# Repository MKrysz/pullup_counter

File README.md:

# Pullup Counter

## About

The main purpose of the project was to automatically count and save the amount of pullups I do to evaluate them later using python script. For this purpose I developed a small device mounted onto the bar. Other features include display for showing how many pullups were already done that day and USB serial port for easy to use interface with the device.

## Hardware

### PCB

Schematic and PCB was made in KiCad.

For the power supply I decided that 2 AAA batteries would be the best choice, as they're easily available and have good volumetric energy density. Embedding the Li-Po battery was out of the table, because the project is stationary and charging wouldn't be possible.

As the brain of the device I went with STM32L0 series microcontroller because of following reasons:

- low power consumption and low operating voltage, which is mandatory in battery operated systems like this
- my familiarity with developing both harware and software development with this series
- affordable price.

I chose a STM32L051C8 as I had few of them lying around.

The MCU has a backup battery used for maintaining operation of RTC clock while main batteries are discharged or being replaced. The amount of pullups are displayed on 7 segment display as it's cheap, small and easy to drive. It's also perfect for displaying numbers which is all It's used here for. For a memory in which I would store my database i used a 512kB SPI Flash - P25Q40H. Communication with the device is done with USB serial port, so I included an USB port and USB-UART converter. I also included a capacitive touch pad and little sensor IC as a way to wake the device up. For detecting pullups I used proximity sesor consisting of IR Led diode and photodiode.

PCBs were manufactured by JLCPCB, and are shown below:

During soldering I found out that I'm out of SMD proximity sensors so I glued a THT one instead. Also, by accident, I soldered PNP transistors instead of NPN. After replacing the transistors I had to connect them to different pins of the MCU as the original ones were blown up.

After assembling and mounting it on the pullup bar:

### Mounting

Mounting is done using 3D-printed mounting system and four pairs of M3 bolts and nuts.

## Software

### Embedded

Project was made in VSCode using [stm32-for-vscode](https://github.com/bmd-studio/stm32-for-vscode) extension. For this project I used [stm32CubeMX](https://www.st.com/en/development-tools/stm32cubemx.html) for generating initialization code. I've also used nimaltd's [drivers for SPI flash memory](https://github.com/nimaltd/w25qxx).

The device must be woken up before every training session, which can be done either by physical button or capacitive touch pad. After that if device haven't detected a pullup within specified time, it goes back to sleep to prolong battery life.

Every pullup series is represented with following struct

```C

typedef struct _entry_struct
{
    uint32_t id; // unique id
    unsigned int count:6; // amount of pullups done in the series

    // timestamp
    unsigned int minute:6;
    unsigned int hour:5;
    unsigned int day:5;
    unsigned int month:4;
    unsigned int year:6;
}entry_t;

```

Because each entry's size is 8 bytes and my flash memory is 512kB the maximum amount of pullups that can be saved within the device is over 65 thousand

### USB User Interface

User interface allows the user for easy change of important parameters, debugging and downloading and  clearing data from device's flash memory. To put device in interface mode, plug it in your computer and restart it. The welcome message should appear. After that you can type 'help' for a list of available commands with short description.

### Data analysis

Python script that reads and interprets data acquired from the device.

Below are shown examples of generated plots:

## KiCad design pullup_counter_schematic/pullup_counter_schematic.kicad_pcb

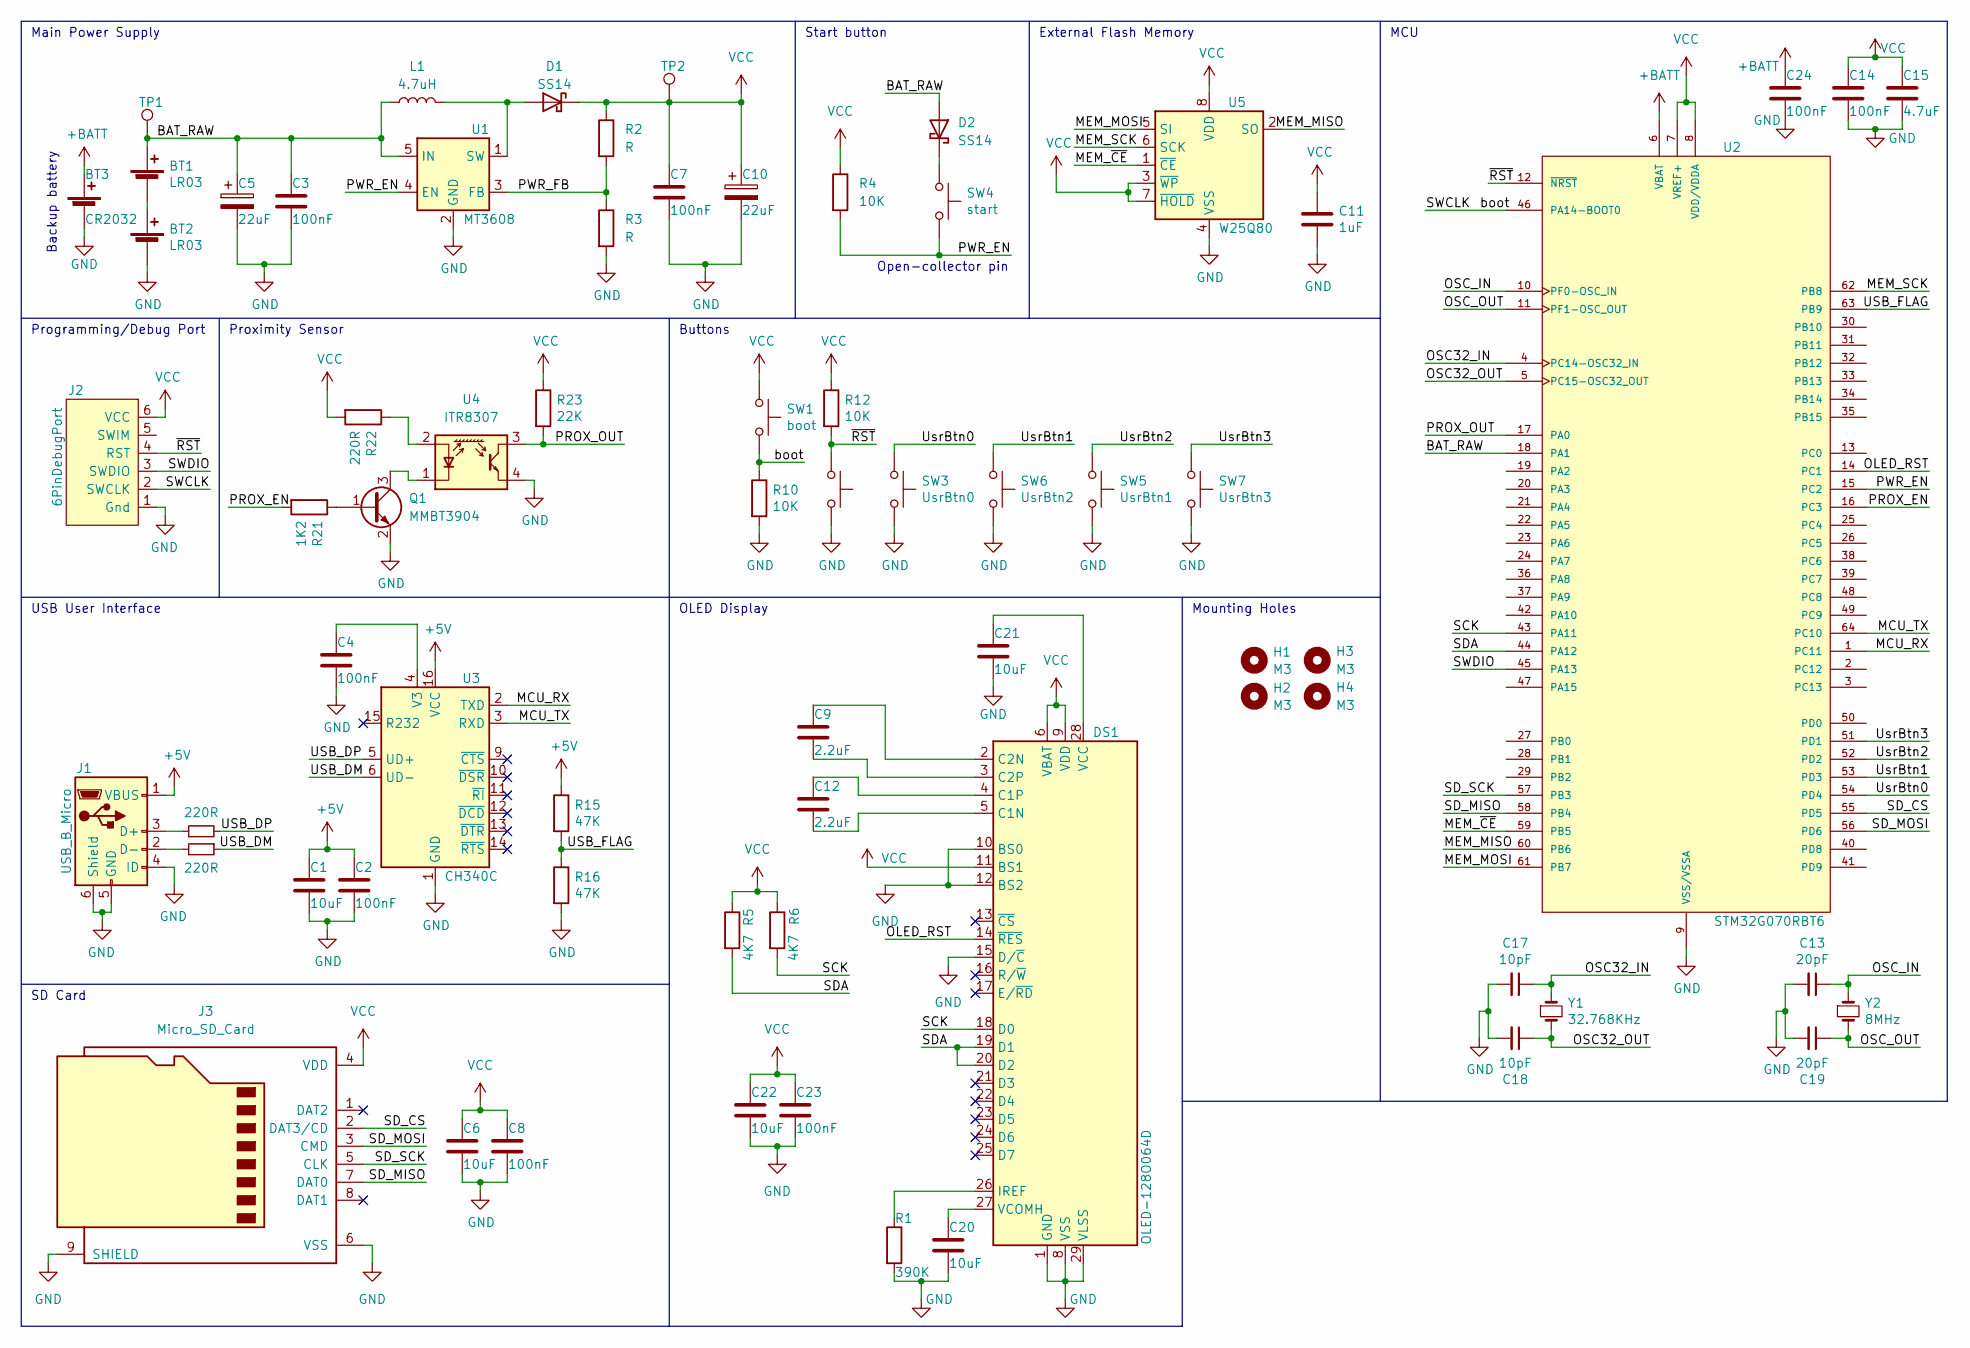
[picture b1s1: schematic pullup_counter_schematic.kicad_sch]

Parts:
BT1, BT2: LR03; SMD_SMT_AAA_LR03
BT3: CR2032; CR2032_CR2025_Battery_Holder
C1, C6, C20, C21, C22: 10uF; C_0805_2012Metric_Pad1.18x1.45mm_HandSolder
C2, C3, C4, C7, C8, C14, C23, C24: 100nF; C_0805_2012Metric_Pad1.18x1.45mm_HandSolder
C5, C10: 22uF; CP_Elec_5x4.5
C9, C12: 2.2uF; C_0805_2012Metric_Pad1.18x1.45mm_HandSolder
C11: 1uF; C_0805_2012Metric_Pad1.18x1.45mm_HandSolder
C13, C19: 20pF; C_0603_1608Metric_Pad1.08x0.95mm_HandSolder
C15: 4.7uF; C_0805_2012Metric_Pad1.18x1.45mm_HandSolder
C17, C18: 10pF; C_0603_1608Metric_Pad1.08x0.95mm_HandSolder
D1, D2: SS14; D_SMA
DS1: OLED-128O064D
H1, H2, H3, H4: M3; MountingHole_3.2mm_M3
J1: USB_B_Micro; USB_Micro-B_Amphenol_10118194_Horizontal
J2: 6PinDebugPort; IDC-Header_2x03_P2.54mm_Vertical
J3: Micro_SD_Card; uSD_socket
L1: 4.7uH; L_Ferrocore_DLG-0403
Q1: MMBT3904; SOT-23
R1: 390K; R_0805_2012Metric_Pad1.20x1.40mm_HandSolder
R2, R3: R; R_0805_2012Metric_Pad1.20x1.40mm_HandSolder
R4, R10, R12: 10K; R_0805_2012Metric_Pad1.20x1.40mm_HandSolder
R5, R6: 4K7; R_0805_2012Metric_Pad1.20x1.40mm_HandSolder
R8, R9, R22: 220R; R_0805_2012Metric_Pad1.20x1.40mm_HandSolder
R15, R16: 47K; R_0805_2012Metric_Pad1.20x1.40mm_HandSolder
R21: 1K2; R_0805_2012Metric_Pad1.20x1.40mm_HandSolder
R23: 22K; R_0805_2012Metric_Pad1.20x1.40mm_HandSolder
SW1: boot; TSB008
SW2: rst; TSB008
SW3: UsrBtn0; TSB008
SW4: start; sw_push_12_x_12_mm
SW5: UsrBtn1; TSB008
SW6: UsrBtn2; TSB008
SW7: UsrBtn3; TSB008
TP1, TP2: PinSocket_1x01_P2.54mm_Vertical
U1: MT3608; SOT-23-6
U2: STM32G070RBT6; LQFP-64_10x10mm_P0.5mm; PARTREV 1
U3: CH340C; SOIC-16_3.9x9.9mm_P1.27mm
U4: ITR8307; Everlight_ITR8307
U5: W25Q80; SOIC-8_5.275x5.275mm_P1.27mm
Y1: 32.768KHz; Crystal_HC49-4H_Vertical
Y2: 8MHz; Crystal_HC49-4H_Vertical

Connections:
+5V: C1.1, C2.1, J1.1 (VBUS), R15.1, U3.16 (VCC)
+BATT: BT3.1 (+), C24.1, U2.6 (VBAT)
/BAT_RAW: BT1.1 (+), C3.1, C5.1, D2.2 (A), L1.1, TP1.1, U1.5 (IN), U2.18 (PA1)
/MCU_RX: U2.1 (PC11), U3.2 (TXD)
/MCU_TX: U2.64 (PC10), U3.3 (RXD)
/MEM_MISO: U2.60 (PB6), U5.2 (SO)
/MEM_MOSI: U2.61 (PB7), U5.5 (SI)
/MEM_SCK: U2.62 (PB8), U5.6 (SCK)
/MEM_~CE: U2.59 (PB5), U5.1 (~CE)
/OLED_RST: DS1.14 (~RES), U2.14 (PC1)
/OSC32_IN: C17.1, U2.4 (PC14-OSC32_IN), Y1.1
/OSC32_OUT: C18.1, U2.5 (PC15-OSC32_OUT), Y1.2
/OSC_IN: C13.1, U2.10 (PF0-OSC_IN), Y2.1
/OSC_OUT: C19.1, U2.11 (PF1-OSC_OUT), Y2.2
/PROX_EN: R21.2, U2.16 (PC3)
/PROX_OUT: R23.2, U2.17 (PA0), U4.3 (C)
/PWR_EN: R4.2, SW4.2, U1.4 (EN), U2.15 (PC2)
/PWR_FB: R2.2, R3.1, U1.3 (FB)
/SCK: DS1.18 (D0), R6.2, U2.43 (PA11)
/SDA: DS1.19 (D1), DS1.20 (D2), R5.2, U2.44 (PA12)
/SD_CS: J3.2 (DAT3/CD), U2.55 (PD5)
/SD_MISO: J3.7 (DAT0), U2.58 (PB4)
/SD_MOSI: J3.3 (CMD), U2.56 (PD6)
/SD_SCK: J3.5 (CLK), U2.57 (PB3)
/SWCLK: J2.2 (SWCLK), R10.1, SW1.2, U2.46 (PA14-BOOT0)
/SWDIO: J2.3 (SWDIO), U2.45 (PA13)
/USB_DM: R9.1, U3.6 (UD-)
/USB_DP: R8.2, U3.5 (UD+)
/USB_FLAG: R15.2, R16.1, U2.63 (PB9)
/UsrBtn0: SW3.1, U2.54 (PD4)
/UsrBtn1: SW6.1, U2.53 (PD3)
/UsrBtn2: SW5.1, U2.52 (PD2)
/UsrBtn3: SW7.1, U2.51 (PD1)
/~RST: J2.4 (RST), R12.2, SW2.1, U2.12 (~NRST)
GND: BT2.2 (-), BT3.2 (-), C1.2, C2.2, C3.2, C4.2, C5.2, C6.2, C7.2, C8.2, C10.2, C11.2, C13.2, C14.2, C15.2, C17.2, C18.2, C19.2, C20.2, C21.2, C22.2, C23.2, C24.2, DS1.1 (GND), DS1.8 (VSS), DS1.10 (BS0), DS1.12 (BS2), DS1.15 (D/~C), DS1.29 (VLSS), DS1.30 (GND), J1.4 (ID), J1.5 (GND), J1.6 (Shield), J2.1 (Gnd), J3.6 (VSS), J3.9 (SHIELD), Q1.2 (E), R1.2, R3.2, R10.2, R16.2, SW2.2, SW3.2, SW5.2, SW6.2, SW7.2, U1.2 (GND), U2.9 (VSS/VSSA), U3.1 (GND), U4.4 (E), U5.4 (VSS)
unnamed: BT1.2 (-), BT2.1 (+)
unnamed: C4.1, U3.4 (V3)
unnamed: C9.1, DS1.2 (C2N)
unnamed: C9.2, DS1.3 (C2P)
unnamed: C12.1, DS1.4 (C1P)
unnamed: C12.2, DS1.5 (C1N)
unnamed: C20.1, DS1.27 (VCOMH)
unnamed: D1.2 (A), L1.2, U1.1 (SW)
unnamed: D2.1 (K), SW4.1
unnamed: DS1.26 (IREF), R1.1
unnamed: C21.1, DS1.28 (VCC)
unnamed: J1.2 (D-), R9.2
unnamed: J1.3 (D+), R8.1
unnamed: Q1.1 (B), R21.1
unnamed: Q1.3 (C), U4.1 (K)
unnamed: R22.1, U4.2 (A)
VCC: C6.1, C7.1, C8.1, C10.1, C11.1, C14.1, C15.1, C22.1, C23.1, D1.1 (K), DS1.6 (VBAT), DS1.9 (VDD), DS1.11 (BS1), J2.6 (VCC), J3.4 (VDD), R2.1, R4.1, R5.1, R6.1, R12.1, R22.2, R23.1, SW1.1, TP2.1, U2.7 (VREF+), U2.8 (VDD/VDDA), U5.3 (~WP), U5.7 (~HOLD), U5.8 (VDD)

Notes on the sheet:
OLED Display
USB User Interface
Main Power Supply
Programming/Debug Port
Open-collector pin
Backup battery
External Flash Memory
MCU
Start button
Proximity Sensor
Mounting Holes
SD Card
Buttons

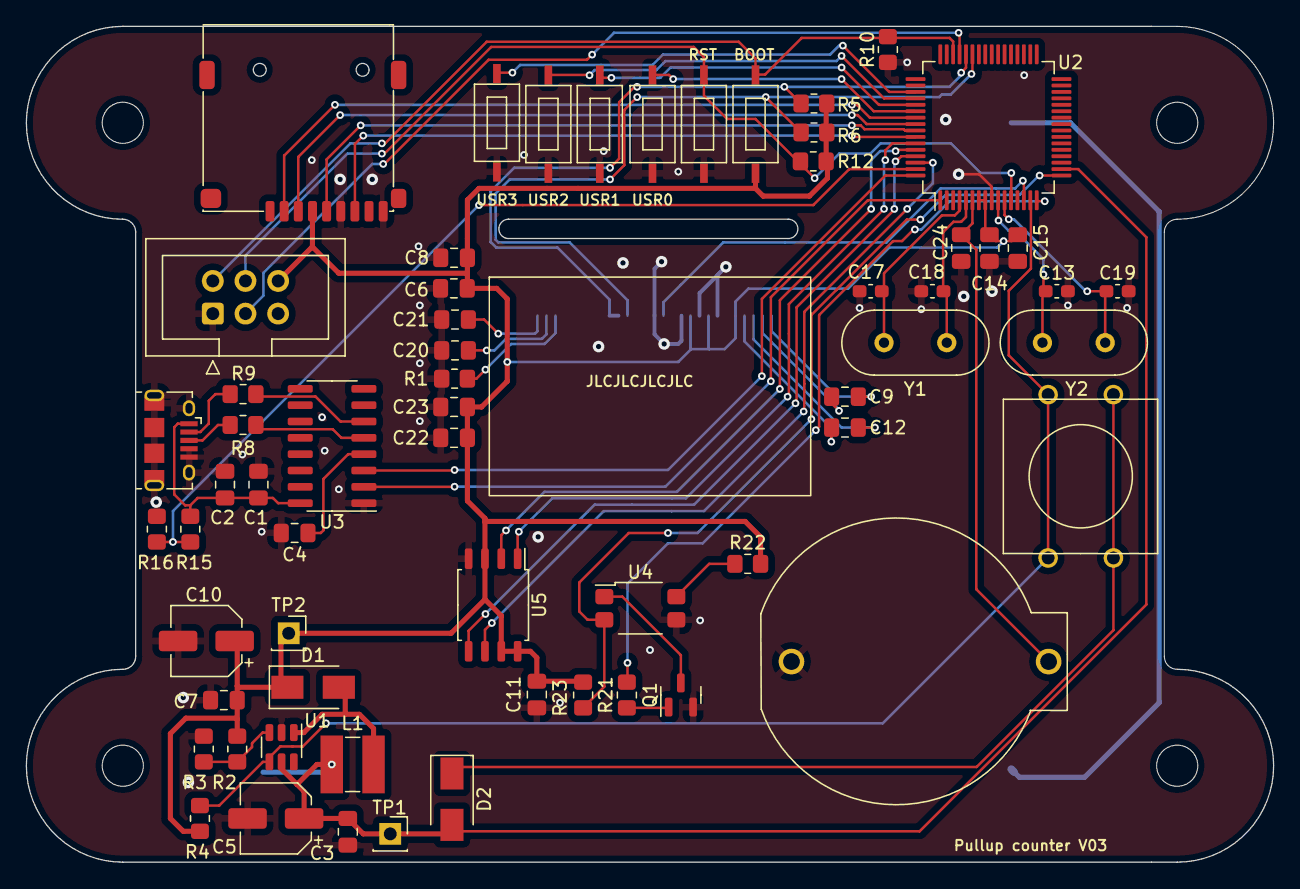
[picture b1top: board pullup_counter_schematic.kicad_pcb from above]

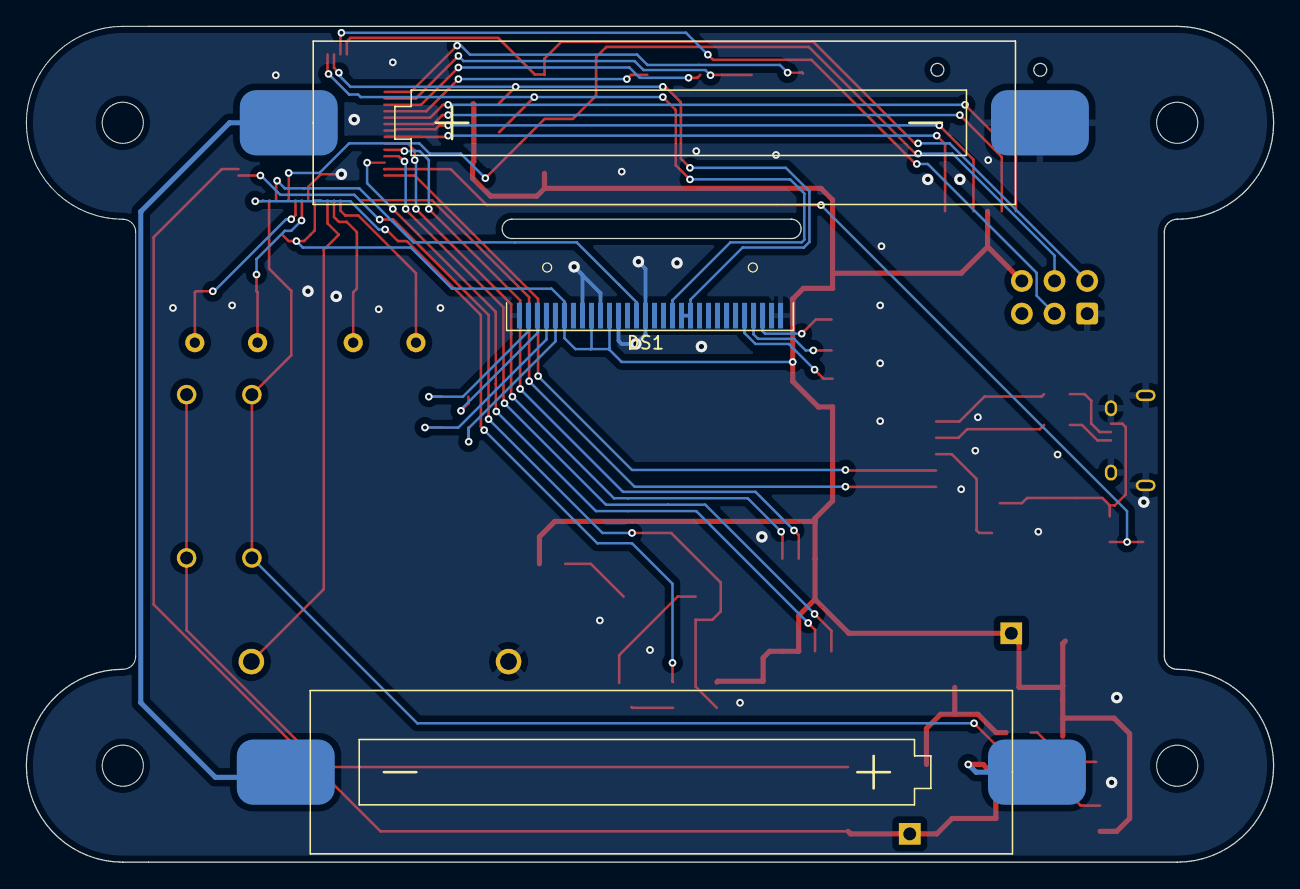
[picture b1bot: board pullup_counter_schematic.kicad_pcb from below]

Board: 2 copper layers, 97.0 x 65.0 mm, 69 parts (2 on the bottom side), 52 nets.

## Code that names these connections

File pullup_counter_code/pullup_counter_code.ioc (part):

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Mcu.Name=STM32G070RBTx
Mcu.Package=LQFP64
Mcu.UserName=STM32G070RBTx
PA0.GPIOParameters=GPIO_Label
PA0.GPIO_Label=PROX_OUT
PA0.Mode=IN0
PA0.Signal=ADC1_IN0
PA1.GPIOParameters=GPIO_Label
PA1.GPIO_Label=BAT_RAW
PA1.Mode=IN1
PA1.Signal=ADC1_IN1
PA11\ [PA9].GPIOParameters=GPIO_Speed,GPIO_Pu
PA11\ [PA9].GPIO_Pu=GPIO_PULLUP
PA11\ [PA9].GPIO_Speed=GPIO_SPEED_FREQ_LOW
PA11\ [PA9].Mode=I2C
PA11\ [PA9].Signal=I2C2_SCL
PA12\ [PA10].GPIOParameters=GPIO_Speed,GPIO_Pu
PA12\ [PA10].GPIO_Pu=GPIO_PULLUP
PA12\ [PA10].GPIO_Speed=GPIO_SPEED_FREQ_LOW
PA12\ [PA10].Mode=I2C
PA12\ [PA10].Signal=I2C2_SDA
PA13.Mode=Serial_Wire
PA13.Signal=SYS_SWDIO
PA14-BOOT0.Mode=Serial_Wire
PA14-BOOT0.Signal=SYS_SWCLK
PB3.Mode=Full_Duplex_Master
PB3.Signal=SPI1_SCK
PB4.Mode=Full_Duplex_Master
PB4.Signal=SPI1_MISO
PB5.GPIOParameters=GPIO_Label
PB5.GPIO_Label=FLASH_CS
PB5.Signal=GPIO_Output
PB6.Mode=Full_Duplex_Master
PB6.Signal=SPI2_MISO
PB7.Mode=Full_Duplex_Master
PB7.Signal=SPI2_MOSI
PB8.Mode=Full_Duplex_Master
PB8.Signal=SPI2_SCK
PB9.GPIOParameters=GPIO_Label
PB9.GPIO_Label=USB_FLAG
PB9.Signal=GPXTI9
PC1.GPIOParameters=PinState,GPIO_Label
PC1.GPIO_Label=OLED_RST
PC1.PinState=GPIO_PIN_SET
PC1.Signal=GPIO_Output
PC10.Mode=Asynchronous
PC10.Signal=USART3_TX
PC11.Mode=Asynchronous
PC11.Signal=USART3_RX
PC2.GPIOParameters=PinState,GPIO_PuPd,GPIO_Label,GPIO_ModeDefaultOutputPP
PC2.GPIO_Label=PWR_EN
PC2.GPIO_ModeDefaultOutputPP=GPIO_MODE_OUTPUT_OD
PC2.GPIO_PuPd=GPIO_NOPULL
PC2.PinState=GPIO_PIN_SET
PC2.Signal=GPIO_Output
PC3.GPIOParameters=GPIO_Label
PC3.GPIO_Label=PROX_EN
PC3.Signal=GPIO_Output
PD1.GPIOParameters=GPIO_PuPd,GPIO_Label,GPIO_ModeDefaultEXTI
PD1.GPIO_Label=UsrBtn3
PD1.GPIO_ModeDefaultEXTI=GPIO_MODE_IT_FALLING
PD1.GPIO_PuPd=GPIO_PULLUP
PD1.Signal=GPXTI1
PD2.GPIOParameters=GPIO_PuPd,GPIO_Label,GPIO_ModeDefaultEXTI
PD2.GPIO_Label=UsrBtn2
PD2.GPIO_ModeDefaultEXTI=GPIO_MODE_IT_FALLING
PD2.GPIO_PuPd=GPIO_PULLUP
PD2.Signal=GPXTI2
PD3.GPIOParameters=GPIO_PuPd,GPIO_Label,GPIO_ModeDefaultEXTI
PD3.GPIO_Label=UsrBtn1
PD3.GPIO_ModeDefaultEXTI=GPIO_MODE_IT_FALLING
PD3.GPIO_PuPd=GPIO_PULLUP
PD3.Signal=GPXTI3
PD4.GPIOParameters=GPIO_PuPd,GPIO_Label,GPIO_ModeDefaultEXTI
PD4.GPIO_Label=UsrBtn0
PD4.GPIO_ModeDefaultEXTI=GPIO_MODE_IT_FALLING
PD4.GPIO_PuPd=GPIO_PULLUP
PD4.Signal=GPXTI4
PD5.GPIOParameters=GPIO_Label
PD5.GPIO_Label=SD_CS
PD5.Signal=GPIO_Output
PD6.Mode=Full_Duplex_Master
PD6.Signal=SPI1_MOSI
PF0-OSC_IN\ (PF0).Mode=HSE-External-Oscillator
PF0-OSC_IN\ (PF0).Signal=RCC_OSC_IN
PF1-OSC_OUT\ (PF1).Mode=HSE-External-Oscillator
PF1-OSC_OUT\ (PF1).Signal=RCC_OSC_OUT
RCC.HSE_VALUE=8000000
RCC.SYSCLKFreq_VALUE=64000000
RCC.SYSCLKSource=RCC_SYSCLKSOURCE_PLLCLK
board=custom

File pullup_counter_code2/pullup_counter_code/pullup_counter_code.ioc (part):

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Mcu.Name=STM32L051C(6-8)Tx
Mcu.Package=LQFP48
Mcu.UserName=STM32L051C8Tx
PA0.GPIOParameters=GPIO_Label
PA0.GPIO_Label=DISTANCE
PA0.Mode=IN0
PA0.Signal=ADC_IN0
PA10.GPIOParameters=GPIO_Label
PA10.GPIO_Label=dis_f
PA10.Signal=GPIO_Output
PA11.GPIOParameters=GPIO_Label
PA11.GPIO_Label=dis_sel_1
PA11.Signal=GPIO_Output
PA12.GPIOParameters=GPIO_Label
PA12.GPIO_Label=dis_sel_0
PA12.Signal=GPIO_Output
PA13.Mode=Serial_Wire
PA13.Signal=SYS_SWDIO
PA14.Mode=Serial_Wire
PA14.Signal=SYS_SWCLK
PA15.GPIOParameters=GPIO_Label
PA15.GPIO_Label=BAT_SENSE_EN
PA15.Signal=GPIO_Output
PA2.Mode=Asynchronous
PA2.Signal=USART2_TX
PA3.Mode=Asynchronous
PA3.Signal=USART2_RX
PA5.Mode=Full_Duplex_Master
PA5.Signal=SPI1_SCK
PA6.Mode=Full_Duplex_Master
PA6.Signal=SPI1_MISO
PA7.Mode=Full_Duplex_Master
PA7.Signal=SPI1_MOSI
PA8.GPIOParameters=GPIO_Label
PA8.GPIO_Label=dis_a
PA8.Signal=GPIO_Output
PA9.GPIOParameters=GPIO_Label
PA9.GPIO_Label=dis_b
PA9.Signal=GPIO_Output
PB0.GPIOParameters=GPIO_Label
PB0.GPIO_Label=CE
PB0.Signal=GPIO_Output
PB1.GPIOParameters=GPIO_Label
PB1.GPIO_Label=BAT_SENSE
PB1.Mode=IN9
PB1.Signal=ADC_IN9
PB12.GPIOParameters=GPIO_Label
PB12.GPIO_Label=dis_c
PB12.Signal=GPIO_Output
PB13.GPIOParameters=GPIO_Label
PB13.GPIO_Label=dis_e
PB13.Signal=GPIO_Output
PB14.GPIOParameters=GPIO_Label
PB14.GPIO_Label=dis_d
PB14.Signal=GPIO_Output
PB15.GPIOParameters=GPIO_Label
PB15.GPIO_Label=dis_g
PB15.Signal=GPIO_Output
PB7.GPIOParameters=GPIO_Label
PB7.GPIO_Label=START
PB7.Signal=GPXTI7
PB8.GPIOParameters=GPIO_Label
PB8.GPIO_Label=TouchPin
PB8.Signal=GPXTI8
PB9.GPIOParameters=GPIO_Label
PB9.GPIO_Label=DISTANCE_EN
PB9.Signal=GPIO_Output
PC13.GPIOParameters=GPIO_Label
PC13.GPIO_Label=USB_FLAG
PC13.Signal=GPIO_Input
PC14-OSC32_IN.Mode=LSE-External-Oscillator
PC14-OSC32_IN.Signal=RCC_OSC32_IN
PC15-OSC32_OUT.Mode=LSE-External-Oscillator
PC15-OSC32_OUT.Signal=RCC_OSC32_OUT
RCC.HSE_VALUE=8000000
RCC.SYSCLKFreq_VALUE=16000000
RCC.SYSCLKSource=RCC_SYSCLKSOURCE_HSI
board=custom

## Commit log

2022-05-13 Upload Version 01
2022-05-13 Uploaded offline work
2022-05-16 Created STM32L051 project
2022-05-16 Created PCB
2022-05-18 Runned DRC and fixed some problems
2022-05-18 Added models
2022-05-27 Generated PCB's Gerbers
2022-06-02 test
    test
2022-06-02 CubeMX is now compatible with schematic
2022-06-02 CubeMX compatible with schematic
2022-06-05 Changed mcu to STM32L051
2022-06-06 Pullup detection routine finished
2022-06-10 User interface work + some minor refactorization
2022-06-10 Calculated value of remaining components
2022-06-12 Display works; UART properly receives data
2022-06-14 CLI improvements; EEPROM fixed;
2022-06-14 External Interrupts now work properly
2022-06-22 Upload of STL model of the clamp
2022-06-22 Ready for deployment
2022-06-24 Added settings and CLI for it
2022-07-16 Minor changes
2022-07-16 Added plot day distribution function
2022-07-17 Added startOfNextDay variable and command for writing entries
2022-07-17 Started writing readme
2022-07-17 Continuation of writing README
2022-07-17 Schematic image now shows up
2022-07-17 Added correct model
2022-07-18 Small changes to README
2022-07-22 Minor changes to the description
2022-07-22 Changed about section of README
2022-07-22 Minor description changes
2022-07-23 Renamed flash CLI functions and added ReadSince
2022-07-26 Python interface for the device created
2022-07-26 Added RTC commands
2022-07-26 Created ConnectAndUpdate routine in python application
2022-07-26 App: interface and dayDistribution plot added
2022-07-26 WeekDistribution plot addded and added placeholder for calendar heatmap
2022-07-29 Changed entry's parameters min and date to minutes and day
2022-07-29 Heatmap calendar works
2022-07-31 Converted stored data to new entry standard
2022-07-31 Application now works with new entry standard
2022-08-11 Firmware now uses new entry standard
2022-08-13 Fixed bug causing the second pullup zeroing display and added config.h
2022-09-12 RTC clock corrected, changed the order of initialization
2022-09-12 Excluded current day from general analysis and cleared the workspace
2023-02-06 Added step-up, SD-Card, OLED display and changed MCU
2023-02-06 Changed proximity sens to SMD, added more USR btns
2023-02-07 Minor fixes
2023-02-08 Generated gerbers for hardware V03
2023-02-08 Generated new CubeMX project with new MCU
2023-02-08 Addded ssd1306, w25qxx libraries and configured them
2023-02-08 Added printf
2023-02-08 Moved headers used from V02. Added a few declarations
2023-02-08 Copied entry.c, changed format to be more .csv friendly
2023-02-09 Added basic declaration/definitions
2023-02-09 Added untested flash functions
2023-02-11 Code changes
2023-02-15 Development continues
2023-02-20 Added ulog library
2023-03-07 Removed ulog
2023-03-07 Updated datasheets
2023-03-07 Started working on new data analyzer
2023-03-07 Deleted unnecessary files in schematic
2023-03-07 Updated used bitmaps
2023-03-12 Started working on SD_update functionality
2023-03-15 SD update finished, created created 'tasks' and handled them
2023-03-15 Data update
2023-03-17 Updated data
2023-03-19 Found duplicate entries
2023-03-25 Trying to fix display
2023-03-27 Display works
2023-03-27 Time between updates is now 150ms
2023-03-29 Fixed SPI Flash; Started work on proximity sensor
2023-07-13 some debugging/schematic fixing
2023-07-14 cleared up kicads libs and footprints
